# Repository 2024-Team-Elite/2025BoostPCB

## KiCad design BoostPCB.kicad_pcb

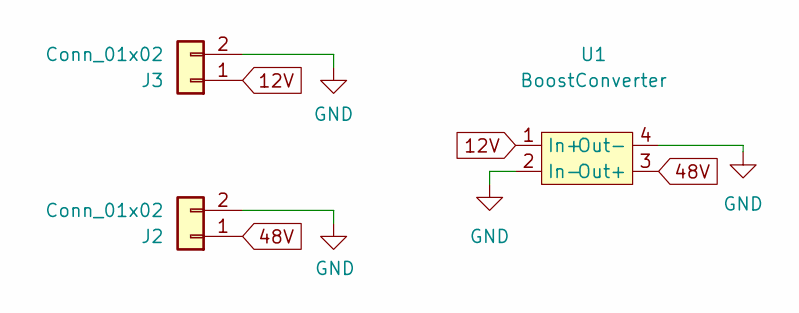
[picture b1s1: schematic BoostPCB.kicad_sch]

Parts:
J2, J3: Conn_01x02; JST_XH_B2B-XH-A_1x02_P2.50mm_Vertical
U1: BoostConverter; Boost_Convertor_LM2577

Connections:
12V: J3.1, U1.1 (In+)
48V: J2.1, U1.3 (Out+)
GND: J2.2, J3.2, U1.2 (In-), U1.4 (Out-)

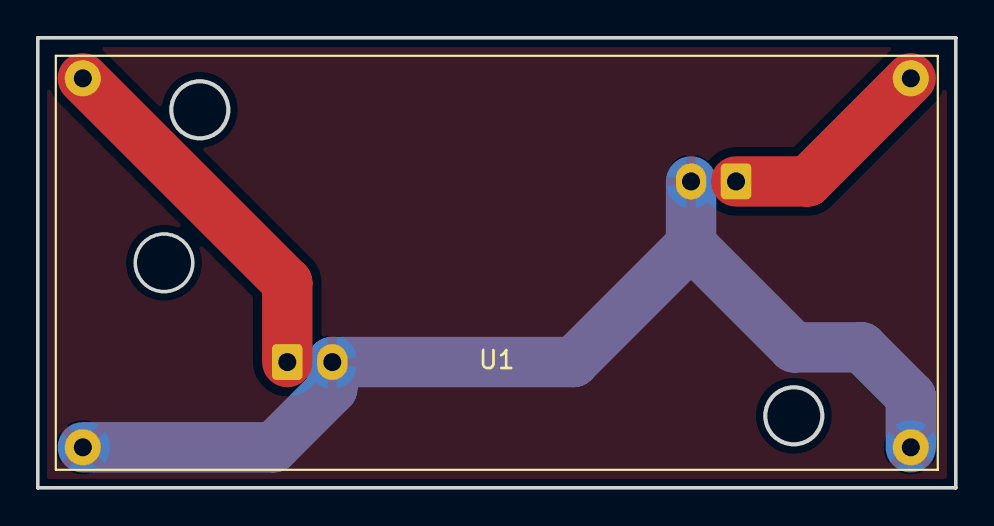
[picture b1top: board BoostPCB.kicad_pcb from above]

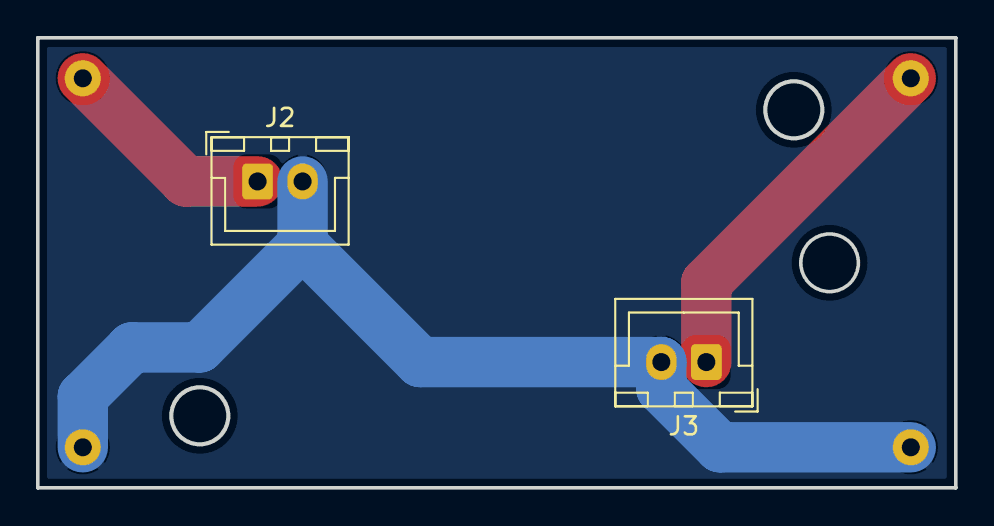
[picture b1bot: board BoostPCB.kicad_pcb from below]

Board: 2 copper layers, 51.0 x 25.0 mm, 3 parts (2 on the bottom side), 3 nets.

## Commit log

2024-11-15 Finished PCB
2024-11-15 made gerbers
